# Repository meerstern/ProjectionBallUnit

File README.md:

# 簡易レーザープロジェクタ ProjectionBall Unit

## 概要 
  * ロボット制御技術を応用したガルバノスキャナ方式の簡易レーザープロジェクタです  
  * 文字や時刻、日時、内蔵図形を描画することが可能です  
  * 本体ボタン、PCのCOMポートやUARTを介して設定を変更することが可能です  
  * 任意の文字列は英数字を最大5文字同時表示、それ以上は32文字までスクロール表示可能です  
  * 投影距離は明るい場所で数m以下、暗い場所で10m以下が目安です  
  * Pico-SDKを使用したソースコードを公開しています  

## 仕様  
  * 電源スイッチ、モード切替、パターン切替、BOOTボタン、RESETボタンを搭載しています  
  * マイコンRP2040、RTC SD3077、モータFA-130、ドライバTB6612、エンコーダMA732Qを使用しています    
  * 赤色レーザーモジュール(出力1mW以下、ClassⅡ同等品)  
  * 5V/0.8AのUSB電源(micro USB)で動作  
  * 電源LED(青)、エラーLED(オレンジ)を搭載  
  * 時刻(RTC)/設定データ一時保存用電池 CR1220  
  * シリアルポートP1 ボーレート9600bps、データサイズ8bit、パリティ無、ストップ1bitが既定値
  * サイズ60mm x60mm x 43mm(突起部、USBコネクタ除く)、固定穴45mm x45mm M3x4

## アプリケーション例
  * 移動ロボットに組込して進路を表示  
  * イベント等での情報を表示  

## 注意点
  * この製品はclassⅡのレーザーを使用しています  
  * レーザーを使用しているため、光源を直視しないでください
  * 分解や改造をした状態で使用すると非常に危険ですので、お控えください  
  * この製品によって引き起こされることについては、当社は責任を持ちません  
  * 目にレーザー光が入る可能性があるため、人や動物に対して投影しないでください    
  * 汎用モータを使用しているため、描画のちらつきや崩れがあります    
  * ガルバノミラーはガラス製表面鏡のため、怪我をする恐れがあります 手を触れなでください  
  * 光軸がずれる可能性があるため、落下や衝撃を与えないでください  
  * 本製品は研究、開発目的の用途を想定しています  
  * 起動後にエラーLEDが点灯する場合はミラー部分が回転できるか、引っかかりがないか確認し、電源を入れ直してください    
  * 告知なしに部品や仕様を変更する場合があります  

## 使い方
### a.単体で使用する場合  
　microUSBをUSB電源等に接続し、電源スイッチ、モード切替、パターン切替スイッチで操作することが可能です    

### b.他の機器と連携する場合  
　microUSBをUSB電源等に接続し、P1端子を介してUART通信(ボーレート9600bps, 3.3V)可能です  
  マイコン等からコマンドを送信して制御することが可能です  

### c.設定を行う場合
　PC等にmicroUSBを接続し、Teraterm等からシリアルポートを介してコマンドで設定を行うことが可能です  

### d.ファームウェアの書換を行う場合
　PC等にmicroUSBを接続し、BOOTボタンを押した状態でRSTボタンを押すとUSBドライブとして認識されます  
  ファームウェアファイル(*.uf2)を認識されたUSBドライブに書き込むことでファームの書換が可能です  

## 描画モード

  * パターン0: 星
  * パターン1: 矢印
  * パターン2: メール
  * パターン3: スマイル
  * パターン4: 太陽
  * パターン5: 雲
  * パターン6: 傘
  * パターン7: 雪だるま
  * パターン8: 雲と雷
  * パターン9: ハート  

## 描画パターン   
  * モード0: 通常描画
  * モード1: 一筆書き描画
  * モード2: 回転描画
  * モード3: デジタル時計
  * モード4: デジタル日付
  * モード5: 任意メッセージ  
※メッセージは英数字、最大5文字、それ以上はスクロール表示です  

## 描画例

## 各部機能

## コマンド
  * コマンド文字列を送信することで描画モードやパターン等の設定が可能です  
  * 改行コードは"\r\n"がデフォルトです  

### 日時設定コマンド  
| コマンド名 | コマンド | 引数 | 例 | 
|:-----------|:------------|:------------|:------------|
| 時刻設定 | tim= | hhmmss | tim=220212(Enterキー) |
| 時刻確認 | tim? | なし | tim?(Enterキー) |
| 日時設定 |	day= | YYMMDD | day=220305(Enterキー) | 
| 日時確認 |	day? | なし | day?(Enterキー) | 	

※日付時刻は必ずそれぞれ2桁で入力してください  
　例　2時8分01秒→tim=020801 

### 制御コマンド  
| コマンド名 | コマンド | 引数 | 例 | 
|:-----------|:------------|:------------|:------------|
| モード確認 |	mod? | なし | mod?(Enterキー) |   
| モード設定 |	mod= | モード | mod=1(Enterキー) |   
| パターン確認 |	ptn? | なし | ptn?(Enterキー) |   
| パターン設定 |	ptn= | パターン| ptn=2(Enterキー) |   
| ソフトリセット | rst! | なし | rst!(Enterキー) |  
| 描画一時停止 | pus! | なし | pus!(Enterキー) |
| 描画再開 |	rsm! | なし | rsm!(Enterキー) | 
| 描画角設定 |	deg= | 角度 | deg=90(Enterキー) | 	
| 描画角確認 |	deg? | なし | deg?(Enterキー) | 	

※描画角は描画の上下左右等の角度を変更する場合に使用します  
※描画角のデフォルトは0度(deg=0)です  

### ユーザ設定コマンド  
| コマンド名 | コマンド | 引数 | 例 | 
|:-----------|:------------|:------------|:------------|
| 描画文字列確認 |	str? | なし | str?(Enterキー) |   
| 描画文字列設定(MEM) |	str= | 英数字 | str=Hello(Enterキー) |   
| 描画文字列設定(RAM) |	stg= | 英数字 | stg=Hello(Enterキー) |  

※MEMの場合、文字列はメモリに保存され、自動的に再起動します  
※RAMの場合、文字列は即時反映されますが、電源再投入等でメモリに保存された文字列に戻ります  

### タイマ設定コマンド  
| コマンド名 | コマンド | 引数 | 例 | 
|:-----------|:------------|:------------|:------------|
| タイマ確認 |	tst? | なし | tst?(Enterキー) |   
| タイマ有効化 | ten! | なし | ten!(Enterキー) |  
| タイマ無効化 | tds! | なし | tds!(Enterキー) |
| 停止時刻確認 |	pus? | なし | pus?(Enterキー) | 
| 停止時刻設定 |	pus= | hhmm | pus=1230(Enterキー) | 
| 再開時刻確認 |	rsm? | なし | pus?(Enterキー) | 
| 再開時刻設定 |	rsm= | hhmm | pus=1530(Enterキー) | 

※タイマ確認は0で無効状態、1で有効状態を示しています  

### キャリブレーションコマンド  
| コマンド名 | コマンド | 引数 | 例 | 
|:-----------|:------------|:------------|:------------|  
| 描画中心確認 |	cen? | なし | cen?(Enterキー) |   
| 描画中心設定 |	cen= | X,Y | cen=100,-200(Enterキー) |   

※レーザーが基板や筐体に当たって描画が隠れてしまう場合にのみ、描画中心を調整します  
※描画中心のキャリブレーション値は出荷時に調整しています    
※キャリブレーション値は初期値に対してX軸(縦方向)、Y軸(横方向)のオフセット値を設定します  

### エラーLED点灯時の確認
  * 起動後にエラーLEDが点灯する場合はミラー部分が回転できるか、引っかかりがないか確認し、電源を入れ直してください
  * ミラーが回転して描画を開始しない場合は下記の図のようにミラーの角度を調整して電源を入れ直してください
  * 手前から見てレーザーモジュールからの光がX軸ミラー、Y軸ミラーの2つのミラーに反射する角度に調整します  
  * ミラーはガラス製のため、怪我の恐れがあります  手を触れないように注意してください   

### 電池交換時の確認
  * RTC電池は電源供給なしで3年以上、日時、時刻及び設定情報を保持することが可能です
  * 万一、保持できなくなった場合はCR1220の電池交換を行ってください
  * 設定情報はモード、パターン、タイマ状態、描画角を保持しています
  * 電池交換後は日時、時刻及び設定情報が不定値となるため、必ず時刻、日付、モード、パターン、タイマ状態、描画角を再設定してください  
  * 特に描画角が不定値になると正しく描画されません deg=0(Enterキー)とコマンドを入力して設定してください

## 外観

License - MIT

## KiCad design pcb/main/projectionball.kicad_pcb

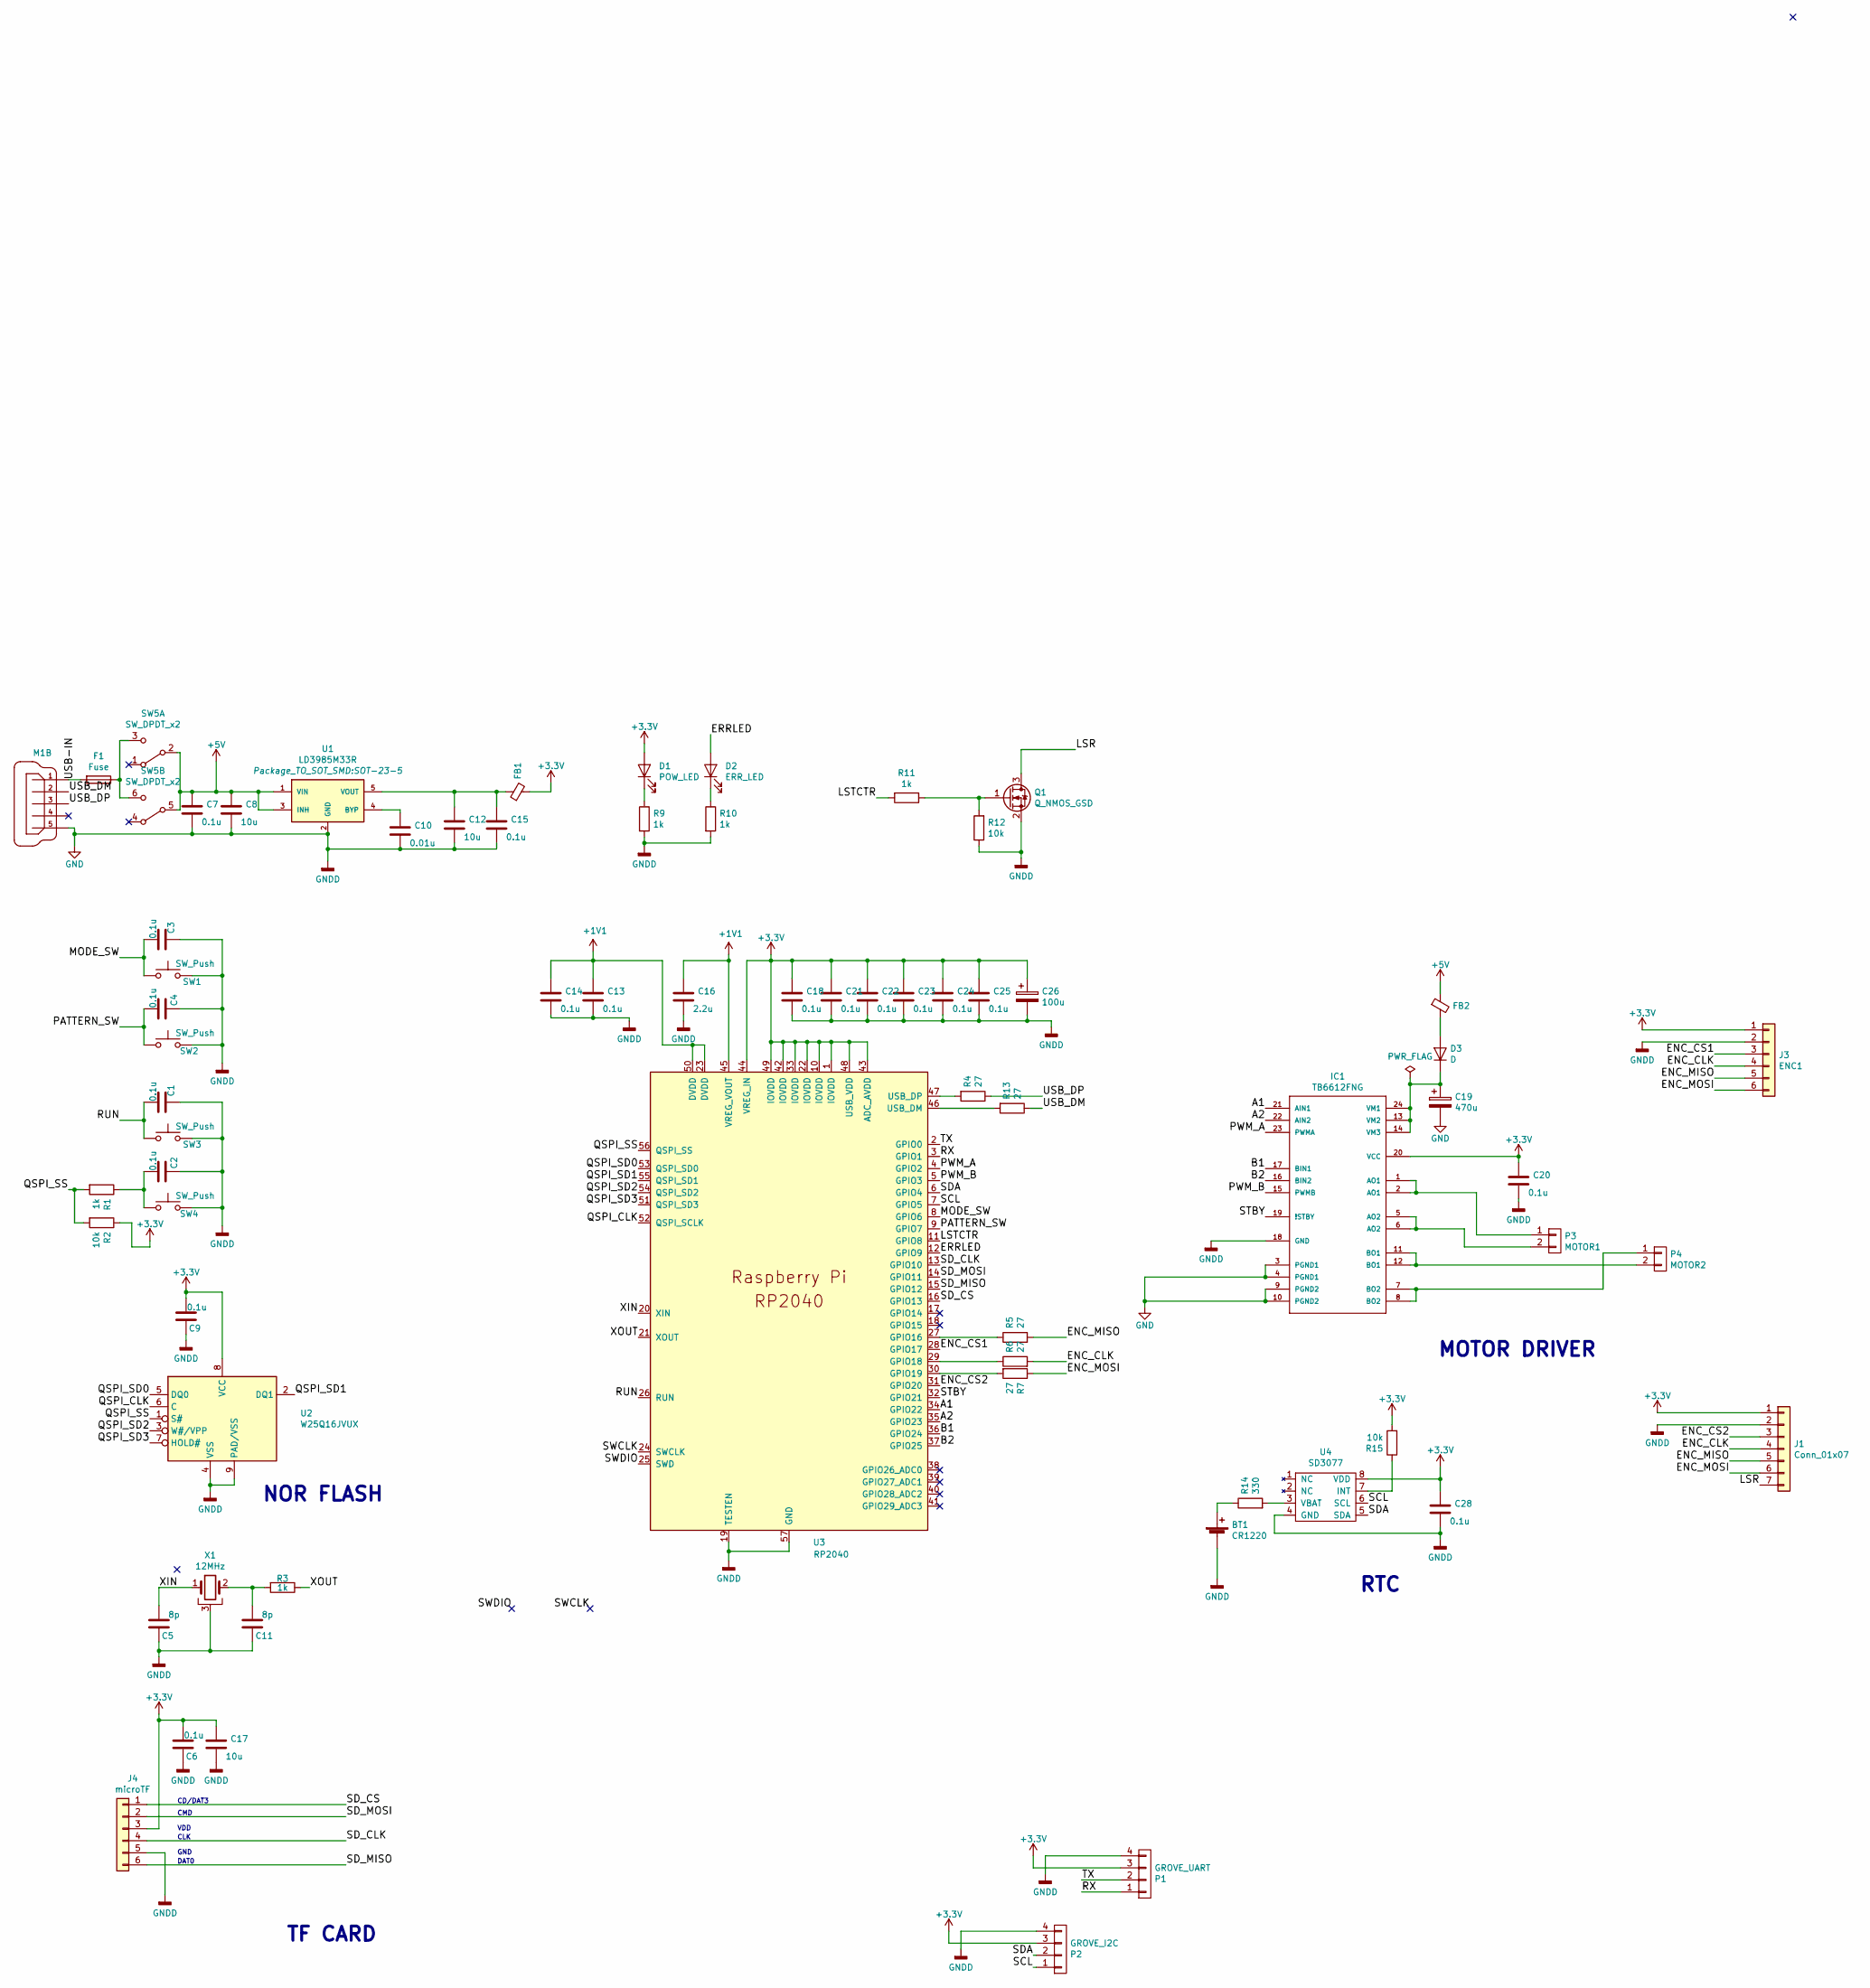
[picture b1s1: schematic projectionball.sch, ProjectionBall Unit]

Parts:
BT1: CR1220; 2895
C1, C2, C3, C4, C6, C7, C9, C13, C14, C15, C18, C20, C21, C22, C23, C24, C25, C28: 0.1u; C_0603_1608Metric
C5, C11: 8p; C_0603_1608Metric
C8, C12, C17: 10u; C_0805_2012Metric
C10: 0.01u; C_0603_1608Metric
C16: 2.2u; C_0603_1608Metric
C19: 470u; CP_Elec_8x10
C26: 100u; CP_Elec_6.3x3.9
D1: POW_LED; LED_0603_1608Metric
D2: ERR_LED; LED_0603_1608Metric
D3: D; D_SOD-123
F1: Fuse; R_1210_3225Metric
FB1, FB2: Ferrite_Bead_Small; L_0603_1608Metric
IC1: TB6612FNG; tb6612-SSOP24
J1: Conn_01x07; PinHeader_1x07_P2.54mm_Vertical
J3: ENC1; PinHeader_1x06_P2.54mm_Vertical
J4: microTF; PinHeader_1x06_P2.54mm_Vertical
M1: MICRO-USB-SHIELD-ZX62R-B-5P; CONN-10118194-0001LF-FCI
P1: GROVE_UART; GROVE
P2: GROVE_I2C; GROVE
P3: MOTOR1; PinHeader_1x02_P2.54mm_Vertical
P4: MOTOR2; PinHeader_1x02_P2.54mm_Vertical
Q1: Q_NMOS_GSD; SOT-23
R1, R3, R9, R10, R11: 1k; R_0603_1608Metric
R2, R12, R15: 10k; R_0603_1608Metric
R4, R5, R6, R7, R13: 27; R_0603_1608Metric
R14: 330; R_0603_1608Metric
SW1, SW2, SW3, SW4: SW_Push; SKRPACE010
SW5: SW_DPDT_x2; DPDT_SMD_Large
U1: LD3985M33R; SOT-23-5
U2: W25Q16JVUX; SON-8-1EP_3x2mm_P0.5mm_EP1.4x1.6mm
U3: RP2040; RP2040-QFN-56
U4: SD3077; SO-8_5.3x6.2mm_P1.27mm
X1: 12MHz; FA238V

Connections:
+1V1: C13.1, C14.1, C16.1, U3.23 (DVDD), U3.45 (VREG_VOUT), U3.50 (DVDD)
+3V3: C6.2, C9.2, C17.1, C18.1, C20.1, C21.1, C22.1, C23.1, C24.1, C25.1, C26.1, C28.1, D1.2 (A), FB1.2, IC1.20 (VCC), J1.1, J3.1, J4.3, P1.3, P2.3, R2.1, R15.2, U2.8 (VCC), U3.1 (IOVDD), U3.10 (IOVDD), U3.22 (IOVDD), U3.33 (IOVDD), U3.42 (IOVDD), U3.43 (ADC_AVDD), U3.44 (VREG_IN), U3.48 (USB_VDD), U3.49 (IOVDD), U4.8 (VDD)
+5V: C7.1, C8.1, FB2.1, SW5.2 (B), SW5.5 (B), U1.1 (VIN), U1.3 (INH)
/A1: IC1.21 (AIN1), U3.34 (GPIO22)
/A2: IC1.22 (AIN2), U3.35 (GPIO23)
/B1: IC1.17 (BIN1), U3.36 (GPIO24)
/B2: IC1.16 (BIN2), U3.37 (GPIO25)
/ENC_CLK: J1.4, J3.4, R6.2
/ENC_CS1: J3.3, U3.28 (GPIO17)
/ENC_CS2: J1.3, U3.31 (GPIO20)
/ENC_MISO: J1.5, J3.5, R5.2
/ENC_MOSI: J1.6, J3.6, R7.1
/ERRLED: D2.2 (A), U3.12 (GPIO9)
/LSR: J1.7, Q1.3 (D)
/LSTCTR: R11.2, U3.11 (GPIO8)
/MODE_SW: C3.2, SW1.1, U3.8 (GPIO6)
/PATTERN_SW: C4.2, SW2.1, U3.9 (GPIO7)
/PWM_A: IC1.23 (PWMA), U3.4 (GPIO2)
/PWM_B: IC1.15 (PWMB), U3.5 (GPIO3)
/QSPI_CLK: U2.6 (C), U3.52 (QSPI_SCLK)
/QSPI_SD0: U2.5 (DQ0), U3.53 (QSPI_SD0)
/QSPI_SD1: U2.2 (DQ1), U3.55 (QSPI_SD1)
/QSPI_SD2: U2.3 (W#/VPP), U3.54 (QSPI_SD2)
/QSPI_SD3: U2.7 (HOLD#), U3.51 (QSPI_SD3)
/QSPI_SS: R1.2, R2.2, U2.1 (S#), U3.56 (QSPI_SS)
/RUN: C1.2, SW3.1, U3.26 (RUN)
/RX: P1.1, U3.3 (GPIO1)
/SCL: P2.1, U3.7 (GPIO5), U4.6 (SCL)
/SDA: P2.2, U3.6 (GPIO4), U4.5 (SDA)
/SD_CLK: J4.4, U3.13 (GPIO10)
/SD_CS: J4.1, U3.16 (GPIO13)
/SD_MISO: J4.6, U3.15 (GPIO12)
/SD_MOSI: J4.2, U3.14 (GPIO11)
/STBY: IC1.19 (!STBY), U3.32 (GPIO21)
/TX: P1.2, U3.2 (GPIO0)
/USB-IN: F1.2, M1.1
/USB_DM: M1.2, R13.1
/USB_DP: M1.3, R4.1
/XIN: C5.2, U3.20 (XIN), X1.1
/XOUT: R3.1, U3.21 (XOUT)
GND: BT1.2 (-), C1.1, C2.1, C3.1, C4.1, C5.1, C6.1, C7.2, C8.2, C9.1, C10.2, C11.1, C12.2, C13.2, C14.2, C15.2, C16.2, C17.2, C18.2, C19.2, C20.2, C21.2, C22.2, C23.2, C24.2, C25.2, C26.2, C28.2, IC1.3 (PGND1), IC1.4 (PGND1), IC1.9 (PGND2), IC1.10 (PGND2), IC1.18 (GND), J1.2, J3.2, J4.5, M1.5, P1.4, P2.4, Q1.2 (S), R9.2, R10.2, R12.1, SW1.2, SW2.2, SW3.2, SW4.2, U1.2 (GND), U2.4 (VSS), U2.9 (PAD/VSS), U3.19 (TESTEN), U3.57 (GND), U4.4 (GND), X1.3
unnamed: BT1.1 (+), R14.1
unnamed: C2.2, R1.1, SW4.1
unnamed: C10.1, U1.4 (BYP)
unnamed: C11.2, R3.2, X1.2
unnamed: C12.1, C15.1, FB1.1, U1.5 (VOUT)
unnamed: C19.1, D3.1 (K), IC1.13 (VM2), IC1.14 (VM3), IC1.24 (VM1)
unnamed: D1.1 (K), R9.1
unnamed: D2.1 (K), R10.1
unnamed: D3.2 (A), FB2.2
unnamed: F1.1, SW5.3 (C), SW5.6 (C)
unnamed: IC1.1 (AO1), IC1.2 (AO1), P3.1
unnamed: IC1.5 (AO2), IC1.6 (AO2), P3.2
unnamed: IC1.7 (BO2), IC1.8 (BO2), P4.1
unnamed: IC1.11 (BO1), IC1.12 (BO1), P4.2
unnamed: Q1.1 (G), R11.1, R12.2
unnamed: R4.2, U3.47 (USB_DP)
unnamed: R5.1, U3.27 (GPIO16)
unnamed: R6.1, U3.29 (GPIO18)
unnamed: R7.2, U3.30 (GPIO19)
unnamed: R13.2, U3.46 (USB_DM)
unnamed: R14.2, U4.3 (VBAT)
unnamed: R15.1, U4.7 (INT)

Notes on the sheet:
RTC
MOTOR DRIVER
TF CARD
NOR FLASH
CD/DAT3
CMD
VDD
CLK
GND
DAT0

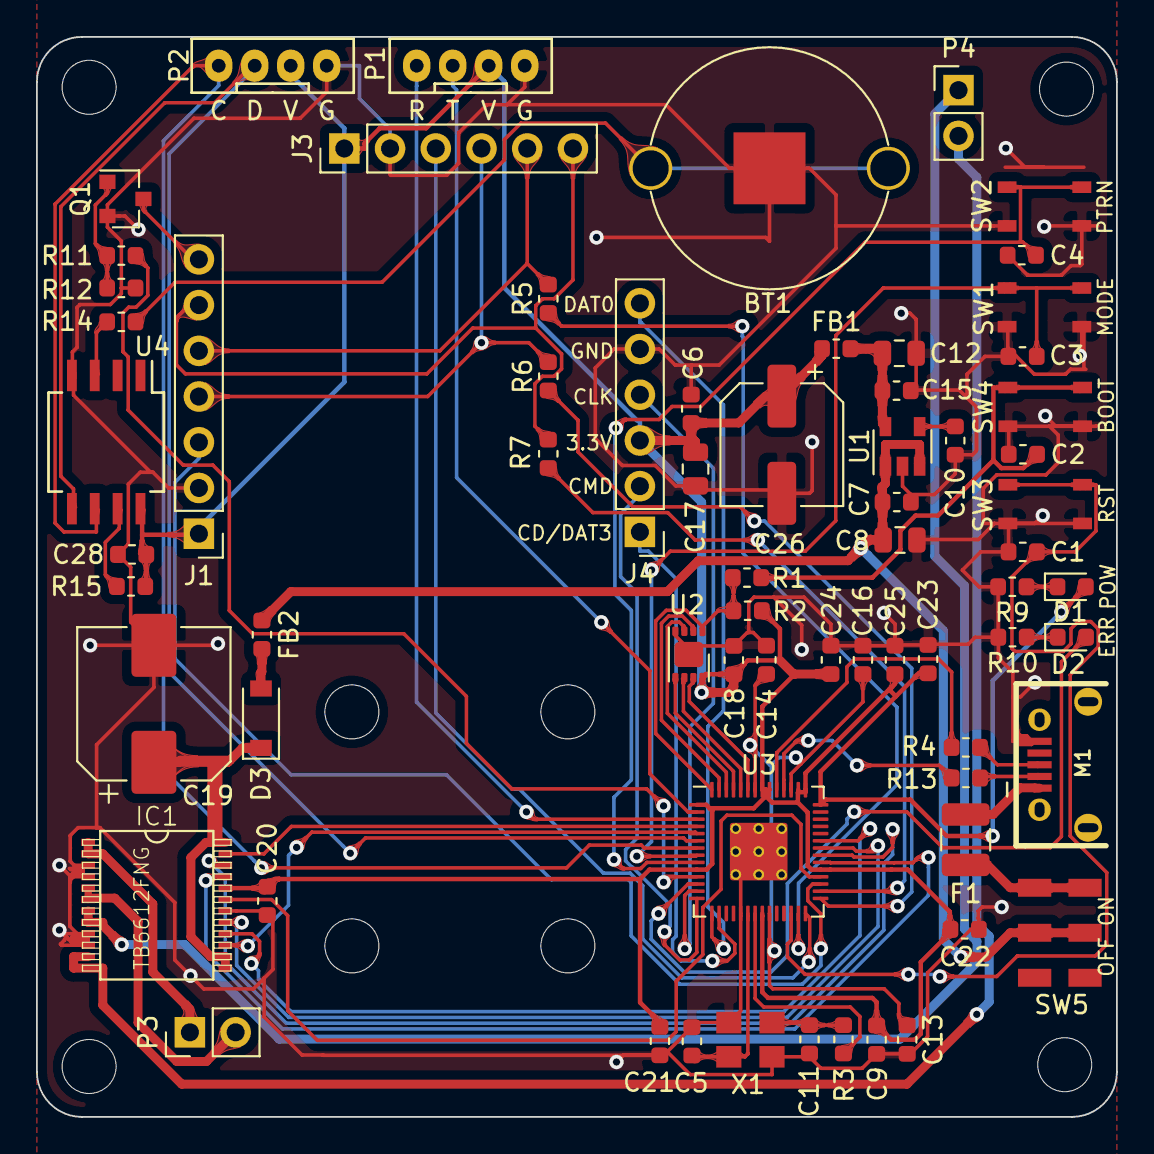
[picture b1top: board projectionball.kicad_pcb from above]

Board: 2 copper layers, 60.0 x 60.0 mm, 76 parts (0 on the bottom side), 63 nets.

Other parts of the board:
REF1, REF2, REF3, REF4, REF9, REF10, REF11, REF12: MountingHole_3mm

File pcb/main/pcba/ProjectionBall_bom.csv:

Comment,Designator,Footprint,LCSC part number,Stock
SW_DPDT_x2,SW5,DPDT_SMD_Large,C115375,
SD3077,U4,SO-8_5.3x6.2mm_P1.27mm,C4748679,
27,"R7,R6,R5,R13,R4",R_0603_1608Metric,C227752,
100u,C26,CP_Elec_6.3x3.9,C2963046,
Q_NMOS_GSD,Q1,SOT-23,C2991132,
Ferrite_Bead_Small,"FB2,FB1",L_0603_1608Metric,C80165,
10u,"C17,C12,C8",C_0805_2012Metric,C380332,
0.1u,"C14,C28,C25,C24,C23,C22,C21,C18,C13,C9,C2,C1,C3,C4,C6,C7,C15,C20",C_0603_1608Metric,C56476,
W25Q16JVUX,U2,SON-8-1EP_3x2mm_P0.5mm_EP1.4x1.6mm,C2843335,
RP2040,U3,RP2040-QFN-56,C2040,
12MHz,X1,FA238V,C2901650,
SW_Push,"SW4,SW3,SW1,SW2",SKRPACE010,C115360,
10k,"R15,R2,R12",R_0603_1608Metric,C209220,
330,R14,R_0603_1608Metric,C103548,
1k,"R3,R1,R9,R10,R11",R_0603_1608Metric,C73797,
2.2u,C16,C_0603_1608Metric,C2691406,
10p,"C11,C5",C_0603_1608Metric,C388068,
0.01u,C10,C_0603_1608Metric,C307346,
470u,C19,CP_Elec_8x10,C2827943,
POW_LED,D1,LED_0603_1608Metric,C89814,
ERR_LED,D2,LED_0603_1608Metric,C90692,
Fuse,F1,R_1210_3225Metric,C20805,
TB6612FNG,IC1,tb6612-SSOP24,C141517,
MICRO-USB-SHIELD-ZX62R-B-5P,M1,CONN-10118194-0001LF-FCI,C132563,
LD3985M33R,U1,SOT-23-5,C46243,
D,D3,D_SOD-123,C129191,

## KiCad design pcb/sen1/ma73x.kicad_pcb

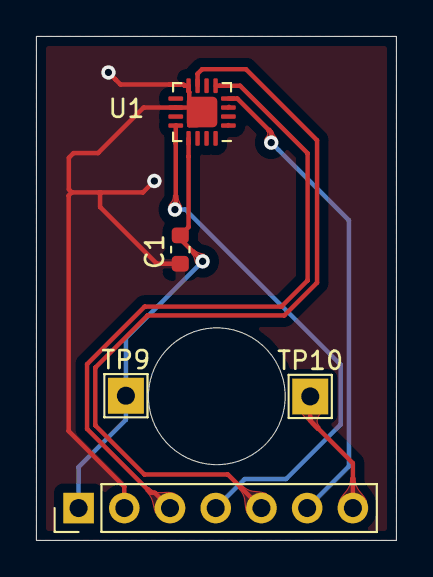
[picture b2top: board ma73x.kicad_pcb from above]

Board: 2 copper layers, 20.0 x 28.0 mm, 5 parts (0 on the bottom side), 7 nets.

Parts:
C1: C; C_0603_1608Metric
J1: Conn_01x07; PinHeader_1x07_P2.54mm_Vertical
TP9: Laser Pow; TestPoint_THTPad_2.0x2.0mm_Drill1.0mm
TP10: Laser GND; TestPoint_THTPad_2.0x2.0mm_Drill1.0mm
U1: MA732; QFN-16-1EP_3x3mm_P0.5mm_EP1.7x1.7mm

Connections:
/3.3V: C1.1, J1.1, TP9.1, U1.13
/CLK: J1.4, U1.12
/CS: J1.3, U1.5
/GND: C1.2, J1.2, U1.8, U1.10, U1.17
/LSR: J1.7, TP10.1
/MISO: J1.5, U1.7
/MOSI: J1.6, U1.4

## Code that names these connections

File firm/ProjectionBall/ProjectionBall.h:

/*
 *  	ProjectionBall.h
 *
 *  Copyright (c) 2023
 *  K.Watanabe, Crescentt
 *  Released under the MIT license
 *  http://opensource.org/licenses/mit-license.php
 *
 */
#ifndef PROJECTIONBALL_H
#define PROJECTIONBALL_H

#define VER_STR     " v1.3"

/* IO Pin Definitions */
#define PIN_TX      0
#define PIN_RX      1
#define PIN_PWM_A	2
#define PIN_PWM_B	3
#define PIN_MODE	6
#define PIN_PATTERN	7
#define PIN_LSR		8
#define PIN_ERR		9
#define PIN_STBY	21
#define PIN_A1		22
#define PIN_A2		23
#define PIN_B1		24
#define PIN_B2		25

#define SPI_PORT spi0

#define PIN_MISO 16
#define PIN_CS1  17
#define PIN_SCK  18
#define PIN_MOSI 19
#define PIN_CS2  20

/* Uart Setting */
#define UART_ID     uart0
#define BAUD_RATE   9600
#define DATA_BITS   8
#define STOP_BITS   1
#define PARITY      UART_PARITY_NONE

/* I2C Setting */
#define I2C_PORT i2c0
#define I2C_SDA 4
#define I2C_SCL 5

/* For Control */
#define ENCODER_BUFFER_SIZE	8
#define ENABLE_RUNAWAY_DETECTION

/* Encoder Type */
#define USE_MA732
//#define USE_AS5048A

/* For Gain Tuning */
#define ENABLE_IN_POS
//#define ENABLE_STEP_CMD

/* RTC Type */
//#define USE_RTC_RV8803
#define USE_RTC_SD30XX

/* For Debug */
//#define ENABLE_ENCODER_CHECK_MODE
#define ENABLE_DEBUG_OUTPUT
//#define ENABLE_DEBUG_INFO
//#define ENABLE_SIN_CMD
//#define ENABLE_FLASH_TEST
#define SIN_CMD_AMP		160


//#define DISABLE_MOTOR
#define ENABLE_PROJECTION_ANGLE

//#define ENABLE_CALIBRATION_MODE


#endif

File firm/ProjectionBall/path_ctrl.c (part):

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
static bool pattern_sw_old = 1;
static bool mode_sw_old = 1;
static bool pattern_sw = 1;
static bool mode_sw = 1;
static bool pattern_update = false;
static bool mode_update = false;

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        case MODE_PATTERN_ONE_STROKE:
            getPatternPath(&step, &allstep, &x0, &x1, &lsr);
            if( lsr == 1 && laser_stroke_cnt <= step )
                lsr = 0;            
            break;

        case MODE_PATTERN_ROTATION:
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
void UpdateUserButton()
{
    pattern_sw = gpio_get(PIN_PATTERN);
    mode_sw = gpio_get(PIN_MODE);
    if(pattern_sw == 1 && pattern_sw_old==0 )
        pattern_update = true;

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
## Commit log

2023-11-21 Add README & IMG
2023-11-21 Add PCB Files
2023-11-21 Add Parts
2023-11-21 Add Footprint Files
2023-11-21 Add Source & Bin Files
2023-11-22 Add Build Files
2023-12-09 Fix bugs
2023-12-09 Add Files
2023-12-12 Update images
2024-02-09 Release v1.3
    ・Improve button response
    ・Improve start up stability
    Release v1.3
